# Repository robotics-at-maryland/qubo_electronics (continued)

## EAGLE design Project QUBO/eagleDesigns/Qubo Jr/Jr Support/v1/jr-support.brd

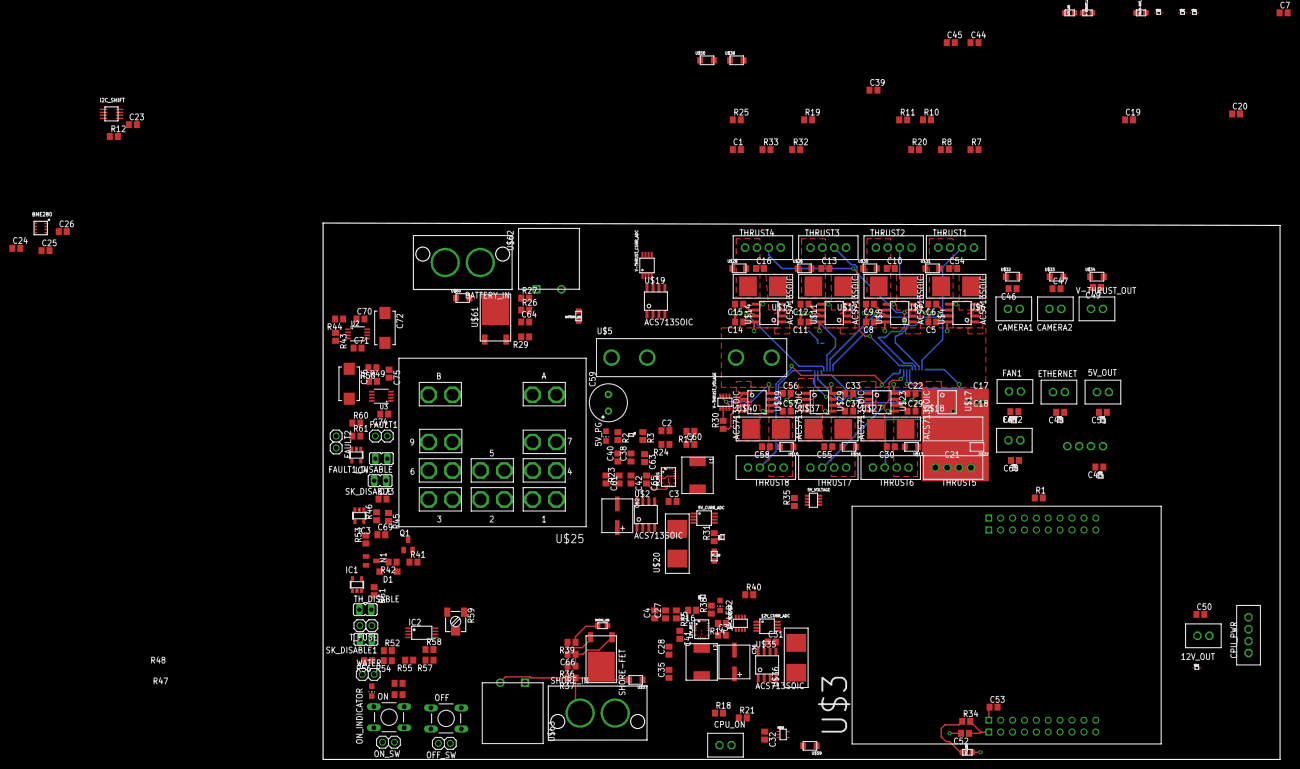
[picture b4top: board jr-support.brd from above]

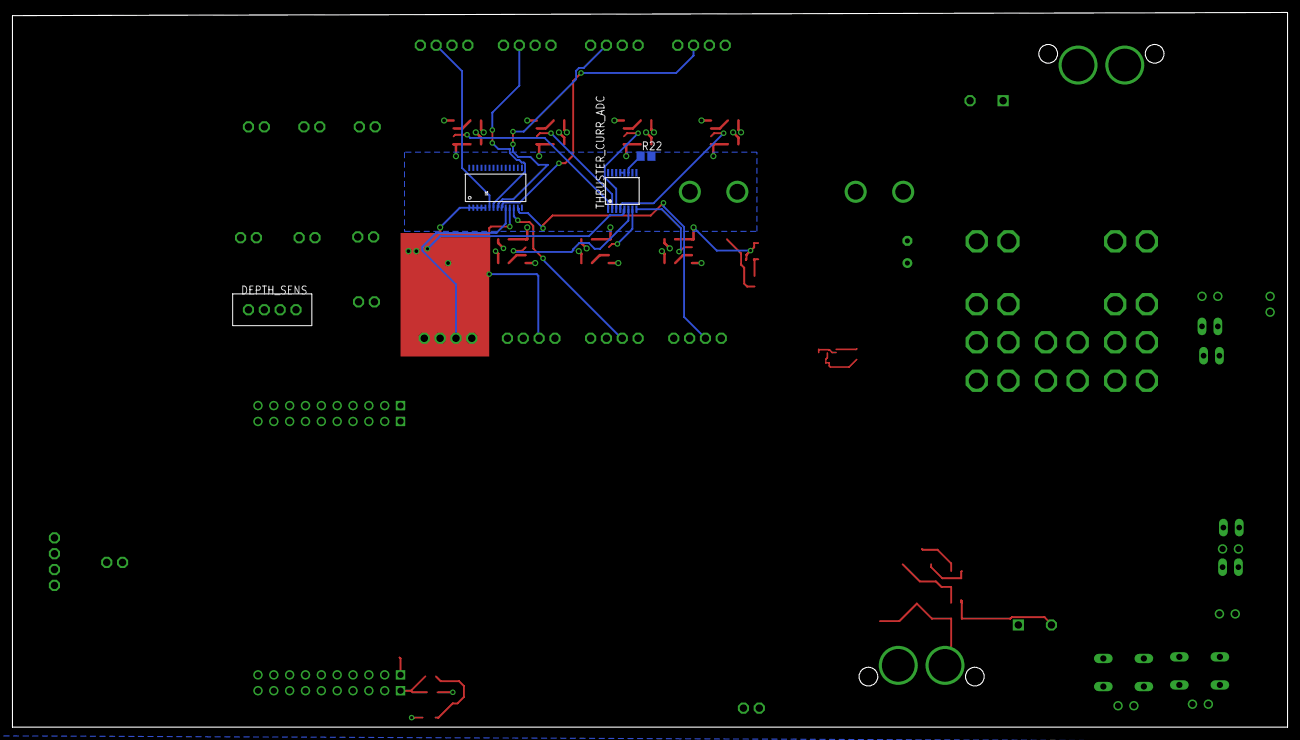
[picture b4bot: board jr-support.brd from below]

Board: 2 copper layers, 204.5 x 114.6 mm, 254 parts (4 on the bottom side), 129 nets.

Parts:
3V3_LED, 5V_LED, 12V_LED: 0805
5V_CURR_ADC, 12V_CURR_ADC: ADC121C021; VSSOP-8
5V_OUT: 5V_OUT; KK254_VERT_2PIN
5V_PG: CHIP-LED0805
5V_REG, 12V_REG: LT8640; QFN18-3X4
5V_VOLTAGE, 12V_VOLTAGE: INA219SOT23; SOT-23-8
12V_OUT: 12V_OUT; KK254_VERT_2PIN
BATTERY_IN: 2_SUPERSABRE; SUPERSABRE_2CIRCUIT
BATTERY_LED: 0805
BME280: BME280; BME280_LGA
C1, C2, C5, C8, C11, C14, C17, C19, C22, C33, C41, C56, C65: 0.1u; C0805
C3, C6, C9, C12, C15, C18, C20, C29, C31, C37, C57: 47n; C0805
C4, C32, C34, C38, C39, C60, C63: 1u; C0805
C7, C10, C13, C16, C21, C30, C43, C44, C45, C46, C47, C48, C49, C50, C51, C52, C53, C54, C55, C58, C67, C68: C0805
C23: 100p; C0805
C24, C25, C26: 100n; C0805
C27, C40: 10u; C0805
C28, C42: 15p; C0805
C35, C61: 22u; C0805
C36, C62: 220u; C-F80
C59: 100u; E3,5-8
C64, C66: 2.2u; C0805
C69, C71, C73, C75: 100nF; C0805
C70, C74: 10nF; C0805
C72, C76: T491D475K050AT; CT7343
CAMERA1, CAMERA2: KK254_VERT_2PIN22-29-2021; KK254_VERT_2PIN
CPU_ON: KK254_VERT_2PIN22-29-2021; KK254_VERT_2PIN
CPU_PWR: CPU PWR; KK254_VERT_4PIN
D1: MMSD4148; SOD123
DEPTH_SENS: Depth Sensor; KK254_VERT_4PIN
ETHERNET: KK254_VERT_2PIN22-29-2021; KK254_VERT_2PIN
FAN1: KK254_VERT_2PIN22-29-2021; KK254_VERT_2PIN
FAN2: Ethernet switch pwr; KK254_VERT_2PIN
FAULT1, FAULT2: 1X02
FAULT1_DISABLE: JP1
I2C_SHIFT: SM8
IC1, IC3, IC4: 74LVC1G08DBV; SOT23-5
IC2: TLC2272PW; TSSOP8
L1, L2: 2.2u; L0740
LED2: FASTCHG; CHIP-LED0805
N1: 2N7002; SOT23
OFF: DTS-6
OFF_SW: 1X02
ON: DTS-6
ON_INDICATOR: Green; CHIP-LED0805
ON_SW: 1X02
Q1: FDN5618P; SOT23
R1, R19, R41, R42, R45, R53, R54: 10k; R0805
R2, R33, R38: 1.2k; R0805
R3, R40, R61: 50k; R0805
R7, R8: 4.7k; R0805
R10, R11: 4.2k; R0805
R12: 200k; R0805
R14, R17: 41.2k; R0805
R15, R23, R46, R49, R51, R60: 1M; R0805
R16: 88.7k; R0805
R18: 510; R0805
R20, R29, R32, R39: 1.5k; R0805
R21: 6.8k; R0805
R22: 0; R0805
R24: 243k; R0805
R25, R30, R35: 10; R0805
R26, R36: 43k; R0805
R27, R37: 4.3k; R0805
R31: 270; R0805
R34: 68; R0805
R43: 845k; R0805
R44, R50: 115k; R0805
R47, R48: 3.3k; R0805
R52, R55, R57, R58: 100k; R0805
R56: 470; R0805
R59: RTRIM3314J
RELAY-OUT_LED: 0805
SHORE-FET: IPD50P04P4-13; TO252-3
SHORE_IN: 2_SUPERSABRE; SUPERSABRE_2CIRCUIT
SHORE_LED: 0805
SK_DISABLE, SK_DISABLE1: JP1
THRUST1, THRUST2, THRUST3, THRUST4, THRUST5, THRUST6, THRUST7, THRUST8: KK254_VERT_4PIN22-29-2041; KK254_VERT_4PIN
THRUSTER_CURR_ADC: ADS7828; TSSOP16
TH_DISABLE: JP1
T_FUSE: 1X02
U1: PCA9685; TSSOP-28_4MM
U2, U3: LT3063; MSOP8
U$1, U$66: DMP32D5SFB; AP02002
U$2, U$4, U$8, U$11, U$14, U$17, U$19, U$23, U$29, U$35, U$39: ACS713SOIC; ACS713-SOIC
U$3: TIVA-C_EVAL
U$5: 25A Fuse; 1.25"_FUSECLIPS
U$6, U$9, U$12, U$15, U$18, U$20, U$27, U$36, U$37, U$40: 4A Fuse; 154-OMNI-BLOK
U$10, U$13, U$16, U$22, U$26, U$28, U$30, U$31, U$32, U$33, U$34, U$38, U$50, U$57, U$59, U$60: VTVS; DO-219AB
U$25: KUHP-5XX1-XX; KUHP_6.35MM-QUICK-CONNECT
U$45: 74LVC1G14; TSSOP5
U$46, U$47, U$48, U$49: ESD9X3; SOD-923_SMD
U$51, U$52, U$53, U$54, U$64, U$65: DESD; X1-DFN1006-2
U$61: IPD50P04P4-13; TO252-3
U$62, U$63: GPTS203212B; GPTS203211B
V-THRUST_CURR_ADC: ADC121C021; VSSOP-8
V-THRUST_LED: 0805
V-THRUST_OUT: Vin_OUT; KK254_VERT_2PIN
V-THRUST_VOLAGE: INA219SOT23; SOT-23-8
WATER: 1X02

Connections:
3V3: BME280.P$2, BME280.P$5, BME280.P$6, BME280.P$8, C24.1, C25.1, C26.1, C52.1, I2C_SHIFT.P$2, R10.2, R11.2, R34.2, U$3.1-1
5V: 5V_CURR_ADC.P$5, 5V_CURR_ADC.P$6, 5V_OUT.P$1, 5V_VOLTAGE.P$4, 12V_CURR_ADC.P$5, 12V_VOLTAGE.P$4, 12V_VOLTAGE.P$8, C1.1, C5.1, C7.1, C8.1, C11.1, C14.1, C17.1, C19.1, C22.1, C33.1, C43.1, C48.1, C51.1, C53.1, C56.1, C67.1, C68.1, DEPTH_SENS.P$4, ETHERNET.P$1, FAN1.P$1, FAN2.P$1, R1.2, R7.2, R8.2, R12.2, R21.2, R31.2, R35.1, THRUSTER_CURR_ADC.10, THRUSTER_CURR_ADC.16, U1.1, U1.2, U1.3, U1.4, U1.5, U1.24, U1.28, U$3.3-1, U$4.P$8, U$8.P$8, U$11.P$8, U$14.P$8, U$17.P$8, U$19.P$8, U$20.P$2, U$23.P$8, U$29.P$8, U$35.P$8, U$39.P$8, U$45.P$5, U$51.P$2, U$52.P$2, U$53.P$2, U$54.P$2, U$64.P$2, U$65.P$2, V-THRUST_CURR_ADC.P$3, V-THRUST_CURR_ADC.P$5, V-THRUST_CURR_ADC.P$6, V-THRUST_VOLAGE.P$4, V-THRUST_VOLAGE.P$7, V-THRUST_VOLAGE.P$8
12V: 12V_OUT.P$1, C44.1, C45.1, C50.1, CPU_PWR.P$3, CPU_PWR.P$4, R25.1, R33.2, U$36.P$2, U$46.P$1, U$47.P$1, U$48.P$1, U$49.P$1
+5V: C69.1, C71.1, FAULT1.1, FAULT1_DISABLE.2, IC2.8, IC3.5, R43.2, R55.1, R57.2, R59.3, R61.2, SK_DISABLE.2, TH_DISABLE.2, T_FUSE.1, U2.3, U2.4
CPU_ON: 12V_REG.14, U$45.P$4
FAULT: IC1.4, IC3.2, IC4.4, OFF.3, OFF.4, OFF_SW.1
FET: IC3.4, N1.1, R53.2
GND: 3V3_LED.P$2, 5V_CURR_ADC.P$3, 5V_CURR_ADC.P$7, 5V_LED.P$2, 5V_OUT.P$2, 5V_PG.C, 5V_REG.6, 5V_REG.7, 5V_REG.10, 5V_REG.11, 5V_REG.18, 5V_VOLTAGE.P$3, 5V_VOLTAGE.P$7, 5V_VOLTAGE.P$8, 12V_CURR_ADC.P$3, 12V_CURR_ADC.P$6, 12V_CURR_ADC.P$7, 12V_LED.P$2, 12V_OUT.P$2, 12V_REG.6, 12V_REG.7, 12V_REG.10, 12V_REG.11, 12V_REG.18, 12V_VOLTAGE.P$3, 12V_VOLTAGE.P$7, BATTERY_IN.P$2, BATTERY_LED.P$2, BME280.P$1, BME280.P$7, C1.2, C2.2, C3.2, C4.2, C5.2, C6.2, C7.2, C8.2, C9.2, C10.2, C11.2, C12.2, C13.2, C14.2, C15.2, C16.2, C17.2, C18.2, C19.2, C20.2, C21.2, C22.2, C23.2, C24.2, C25.2, C26.2, C27.2, C29.2, C30.2, C31.2, C33.2, C34.2, C35.2, C36.P$2, C37.2, C38.2, C39.2, C40.2, C43.2, C44.2, C45.2, C46.2, C47.2, C48.2, C49.2, C50.2, C51.2, C52.2, C53.2, C54.2, C55.2, C56.2, C57.2, C58.2, C59.-, C60.2, C61.2, C62.P$2, C63.2, C64.2, C66.2, C67.2, C68.2, C69.2, C70.2, C71.2, C72.-, C73.2, C74.2, C75.2, C76.-, CAMERA1.P$2, CAMERA2.P$2, CPU_PWR.P$1, CPU_PWR.P$2, DEPTH_SENS.P$3, ETHERNET.P$2, FAN1.P$2, FAN2.P$2, I2C_SHIFT.P$1, IC1.3, IC2.4, IC3.3, IC4.3, LED2.C, N1.2, OFF.1, OFF.2, OFF_SW.2, ON.1, ON.2, ON_INDICATOR.C, ON_SW.2, R14.1, R16.1, R17.1, R19.2, R22.2, R24.1, R44.1, R46.1, R50.1, R51.1, R53.1, R58.1, R59.1, R60.1, RELAY-OUT_LED.P$2, SHORE_IN.P$2, SHORE_LED.P$2, THRUST1.P$1, THRUST1.P$3, THRUST2.P$1, THRUST2.P$3, THRUST3.P$1, THRUST3.P$3, THRUST4.P$1, THRUST4.P$3, THRUST5.P$1, THRUST5.P$3, THRUST6.P$1, THRUST6.P$3, THRUST7.P$1, THRUST7.P$3, THRUST8.P$1, THRUST8.P$3, THRUSTER_CURR_ADC.9, THRUSTER_CURR_ADC.12, THRUSTER_CURR_ADC.13, U1.14, U1.23, U1.25, U2.8, U3.8, U$2.P$5, U$3.2-1, U$3.3-2, U$4.P$5, U$8.P$5, U$10.P$1, U$11.P$5, U$13.P$1, U$14.P$5, U$16.P$1, U$17.P$5, U$19.P$5, U$22.P$1, U$23.P$5, U$26.P$1, U$28.P$1, U$29.P$5, U$30.P$1, U$31.P$1, U$32.P$1, U$33.P$1, U$34.P$1, U$35.P$5, U$38.P$1, U$39.P$5, U$46.P$2, U$47.P$2, U$48.P$2, U$49.P$2, U$50.P$1, U$51.P$1, U$52.P$1, U$53.P$1, U$54.P$1, U$57.P$1, U$60.P$1, U$62.P$1, U$63.P$1, U$64.P$1, U$65.P$1, V-THRUST_CURR_ADC.P$7, V-THRUST_LED.P$2, V-THRUST_OUT.P$2, V-THRUST_VOLAGE.P$3, WATER.2
unnamed: 12V_REG.15, R14.2
unnamed: R1.1, U$3.2-5
unnamed: FAULT2.1, IC4.2, R61.1
unnamed: 5V_PG.A, R2.1
unnamed: R2.2, U$1.P$3
unnamed: 5V_REG.19, R3.1, U$1.P$2
unnamed: 12V_REG.1, C28.1, C35.1, C36.P$1, L2.P$2, R15.2, U$35.P$1, U$35.P$2
unnamed: 5V_REG.15, R17.2
unnamed: C3.1, U$2.P$6
unnamed: C9.1, U$8.P$6
unnamed: C6.1, U$4.P$6
unnamed: C54.1, THRUST1.P$4, U$6.P$2, U$31.P$2
unnamed: U$4.P$3, U$4.P$4, U$6.P$1
unnamed: C10.1, THRUST2.P$4, U$9.P$2, U$30.P$2
unnamed: U$8.P$3, U$8.P$4, U$9.P$1
unnamed: C12.1, U$11.P$6
unnamed: C13.1, THRUST3.P$4, U$12.P$2, U$26.P$2
unnamed: U$11.P$3, U$11.P$4, U$12.P$1
unnamed: C15.1, U$14.P$6
unnamed: C16.1, THRUST4.P$4, U$15.P$2, U$28.P$2
unnamed: R22.1, THRUSTER_CURR_ADC.11
unnamed: U$14.P$3, U$14.P$4, U$15.P$1
unnamed: C18.1, U$17.P$6
unnamed: C21.1, THRUST5.P$4, U$18.P$2, U$22.P$2
unnamed: U$17.P$3, U$17.P$4, U$18.P$1
unnamed: C29.1, U$23.P$6
unnamed: C30.1, THRUST6.P$4, U$13.P$2, U$27.P$2
unnamed: U$23.P$3, U$23.P$4, U$27.P$1
unnamed: C37.1, U$29.P$6
unnamed: 12V_REG.8, 12V_REG.9, 12V_REG.21, 12V_REG.22, C41.2, L2.P$1
unnamed: C20.1, U$19.P$6
unnamed: U$5.P$1, U$5.P$2, U$19.P$3, U$19.P$4
unnamed: R19.1, U$25.AA, U$25.AB
unnamed: C55.1, THRUST7.P$4, U$16.P$2, U$37.P$2
unnamed: U$29.P$3, U$29.P$4, U$37.P$1
unnamed: C57.1, U$39.P$6
unnamed: C58.1, THRUST8.P$4, U$10.P$2, U$40.P$2
unnamed: 5V_REG.8, 5V_REG.9, 5V_REG.21, 5V_REG.22, C65.2, L1.P$1
unnamed: C23.1, I2C_SHIFT.P$7, I2C_SHIFT.P$8, R12.1
unnamed: 5V_REG.20, C42.2, R23.1, R24.2
unnamed: 5V_REG.3, C65.1
unnamed: 12V_REG.20, C28.2, R15.1, R16.2
unnamed: 12V_REG.3, C41.1
unnamed: Q1.1, R41.1, R42.1
unnamed: U$39.P$3, U$39.P$4, U$40.P$1
unnamed: 5V_REG.2, C63.1
unnamed: 12V_VOLTAGE.P$1, 12V_VOLTAGE.P$2, R25.2
unnamed: R37.1, SHORE-FET.TAB, SHORE_IN.P$1, U$57.P$2
unnamed: C32.2, CPU_ON.P$2, U$45.P$3, U$59.P$1
unnamed: C31.1, U$35.P$6
unnamed: U$19.P$7, V-THRUST_CURR_ADC.P$4
unnamed: 12V_REG.2, C39.1
unnamed: U$2.P$3, U$2.P$4, U$20.P$1
unnamed: U$35.P$3, U$35.P$4, U$36.P$1
unnamed: 5V_CURR_ADC.P$4, U$2.P$7
unnamed: R30.2, V-THRUST_VOLAGE.P$1, V-THRUST_VOLAGE.P$2
unnamed: C32.1, R18.2, U$45.P$2
unnamed: 12V_CURR_ADC.P$4, U$35.P$7
unnamed: CPU_ON.P$1, R18.1, R21.1, U$59.P$2
unnamed: C66.1, R36.1, SHORE-FET.1
unnamed: R36.2, R37.2, U$63.P$2
unnamed: BATTERY_IN.P$1, R27.1, U$60.P$2, U$61.TAB
unnamed: C64.1, R26.1, U$61.1
unnamed: R26.2, R27.2, U$62.P$2
unnamed: R20.1, RELAY-OUT_LED.P$1
unnamed: BATTERY_LED.P$1, R29.1
unnamed: 5V_LED.P$1, R31.1
unnamed: R32.1, V-THRUST_LED.P$1
unnamed: 12V_LED.P$1, R33.1
unnamed: 3V3_LED.P$1, R34.1
unnamed: R39.1, SHORE_LED.P$1
unnamed: FAULT1.2, FAULT1_DISABLE.1, IC4.1, R60.2
unnamed: 5V_VOLTAGE.P$1, 5V_VOLTAGE.P$2, R35.2
unnamed: LED2.A, R38.1
unnamed: R38.2, U$66.P$3
unnamed: 12V_REG.19, R40.1, U$66.P$2
unnamed: D1.A, N1.3, R42.2
unnamed: R43.1, R44.2, U2.2
unnamed: C70.1, U2.1
unnamed: ON_INDICATOR.A, R47.1, R48.1
unnamed: R49.1, R50.2, U3.2
unnamed: C74.1, U3.1
unnamed: IC1.2, R51.2, TH_DISABLE.1, T_FUSE.2
unnamed: IC2.2, IC2.7, R52.1
unnamed: IC2.6, R52.2, R54.1
unnamed: IC2.5, R57.1, R58.2
unnamed: R54.2, R55.2, R56.1
unnamed: R56.2, WATER.1
unnamed: IC2.3, R59.2
unnamed: IC2.1, SK_DISABLE1.1
ON_SW: D1.C, ON.3, ON.4, ON_SW.1
RELAY-BATT: Q1.2, R29.2, R41.2, U$25.5A, U$25.5B, U$61.3
RELAY-CTRL: C75.1, R49.2, U3.3, U3.4, U$25.BA, U$25.BB
RELAY-SHORE: R39.2, SHORE-FET.3, U$25.2A, U$25.2B
RELAY_OUT: 5V_REG.4, 5V_REG.13, 5V_REG.14, 12V_REG.4, 12V_REG.13, C4.1, C27.1, C34.1, C38.1, C40.1, C59.+, C60.1, R3.2, R20.2, R40.2, U$1.P$1, U$19.P$1, U$19.P$2, U$25.7A, U$25.7B, U$50.P$2, U$66.P$1
SCL1: 5V_CURR_ADC.P$1, 5V_VOLTAGE.P$5, 12V_CURR_ADC.P$1, 12V_VOLTAGE.P$5, I2C_SHIFT.P$6, R8.1, THRUSTER_CURR_ADC.14, U1.26, U$3.1-9, V-THRUST_CURR_ADC.P$1, V-THRUST_VOLAGE.P$5
SCL-3V3: BME280.P$4, DEPTH_SENS.P$1, I2C_SHIFT.P$3, R11.1
SDA1: 5V_CURR_ADC.P$8, 5V_VOLTAGE.P$6, 12V_CURR_ADC.P$8, 12V_VOLTAGE.P$6, I2C_SHIFT.P$5, R7.1, THRUSTER_CURR_ADC.15, U1.27, U$3.1-10, V-THRUST_CURR_ADC.P$8, V-THRUST_VOLAGE.P$6
SDA-3V3: BME280.P$3, DEPTH_SENS.P$2, I2C_SHIFT.P$4, R10.1
SK: C73.1, IC3.1, R45.1, R46.2, SK_DISABLE.1
SW-5V: 5V_REG.1, C2.1, C42.1, C61.1, C62.P$1, L1.P$2, R23.2, U$2.P$1, U$2.P$2, U$2.P$8
T1_CURR: THRUSTER_CURR_ADC.1, U$4.P$7
T1_PWM: THRUST1.P$2, U1.6
T2_CURR: THRUSTER_CURR_ADC.2, U$8.P$7
T2_PWM: THRUST2.P$2, U1.7
T3_CURR: THRUSTER_CURR_ADC.3, U$11.P$7
T3_PWM: THRUST3.P$2, U1.8
T4_CURR: THRUSTER_CURR_ADC.4, U$14.P$7
T4_PWM: THRUST4.P$2, U1.9
T5_CURR: THRUSTER_CURR_ADC.5, U$17.P$7
T5_PWM: THRUST5.P$2, U1.10
T6_CURR: THRUSTER_CURR_ADC.6, U$23.P$7
T6_PWM: THRUST6.P$2, U1.11
T7_CURR: THRUSTER_CURR_ADC.7, U$29.P$7
T7_PWM: THRUST7.P$2, U1.12
T8_CURR: THRUSTER_CURR_ADC.8, U$39.P$7
T8_PWM: THRUST8.P$2, U1.13
VCC: IC1.5, IC4.5
VDD: C72.+, C76.+, Q1.3, R47.2, R48.2, U2.5, U2.6, U2.7, U3.5, U3.6, U3.7
V_THRUST: C46.1, C47.1, C49.1, CAMERA1.P$1, CAMERA2.P$1, R30.1, R32.2, U$4.P$1, U$4.P$2, U$5.P$3, U$5.P$4, U$8.P$1, U$8.P$2, U$11.P$1, U$11.P$2, U$14.P$1, U$14.P$2, U$17.P$1, U$17.P$2, U$23.P$1, U$23.P$2, U$29.P$1, U$29.P$2, U$32.P$2, U$33.P$2, U$34.P$2, U$38.P$2, U$39.P$1, U$39.P$2, V-THRUST_OUT.P$1
WATER: IC1.1, SK_DISABLE1.2

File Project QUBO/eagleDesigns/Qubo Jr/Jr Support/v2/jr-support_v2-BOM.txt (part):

Partlist exported from C:/Users/Ben/Documents/Dropbox/Documents/UMD/R@M/RAM Tran Electronics_2016/qubo_electronics.git/Project QUBO/eagleDesigns/Jr Support/Jr Support/v2/jr-support_v2.sch at Tue, 5/9/2017 1:04 PM

Part              Value                     Device                    Package                   Description                                                                               PROD_ID  VALUE  
3V3_LED                                     0805_LED                  0805                      LED, 0805 package. Any variety.                                                                           
5V_CURR_ADC       ADC121C021                ADC121C021                VSSOP-8                   ADC121C021 8-pin VSSOP package                                                                            
5V_LED                                      0805_LED                  0805                      LED, 0805 package. Any variety.                                                                           
5V_OUT            5V_OUT                    KK254_VERT_2PIN22-29-2021 KK254_VERT_2PIN           KK® 254 Wire-to-Board Header, Vertical, with Friction Lock, 2 Circuits, Gold (Au) Plating                 
5V_PG                                       LEDCHIP-LED0805           CHIP-LED0805              LED                                                                                                       
5V_REG            LT8640                    LT8640                    QFN18-3X4                 Linear LT8640                                                                                             
5V_VOLTAGE        INA219SOT23               INA219SOT23               SOT-23-8                  TI INA219                                                                                                 
12V_CURR_ADC      ADC121C021                ADC121C021                VSSOP-8                   ADC121C021 8-pin VSSOP package                                                                            
12V_LED                                     0805_LED                  0805                      LED, 0805 package. Any variety.                                                                           
12V_OUT           12V_OUT                   KK254_VERT_2PIN22-29-2021 KK254_VERT_2PIN           KK® 254 Wire-to-Board Header, Vertical, with Friction Lock, 2 Circuits, Gold (Au) Plating                 
12V_REG           LT8640                    LT8640                    QFN18-3X4                 Linear LT8640                                                                                             
12V_VOLTAGE       INA219SOT23               INA219SOT23               SOT-23-8                  TI INA219                                                                                                 
BATTERY_IN        2_SUPERSABRE              2_SUPERSABRE              SUPERSABRE_2CIRCUIT       Molex SuperSabre                                                                                          
BATTERY_LED                                 0805_LED                  0805                      LED, 0805 package. Any variety.                                                                           
BME280            BME280                    BME280                    BME280_LGA                                                                                                          IC-13090 BME280 
C1                0.1u                      C-USC0805                 C0805                     CAPACITOR, American symbol                                                                                
C2                0.1u                      C-USC0805                 C0805                     CAPACITOR, American symbol                                                                                
C3                47n                       C-USC0805                 C0805                     CAPACITOR, American symbol                                                                                
C4                1u                        C-USC0805                 C0805                     CAPACITOR, American symbol                                                                                
C5                0.1u                      C-USC0805                 C0805                     CAPACITOR, American symbol                                                                                
C6                47n                       C-USC0805                 C0805                     CAPACITOR, American symbol                                                                                
C7                                          C-USC0805                 C0805                     CAPACITOR, American symbol                                                                                
C8                0.1u                      C-USC0805                 C0805                     CAPACITOR, American symbol                                                                                
C9                47n                       C-USC0805                 C0805                     CAPACITOR, American symbol                                                                                
C10                                         C-USC0805                 C0805                     CAPACITOR, American symbol                                                                                
C11               0.1u                      C-USC0805                 C0805                     CAPACITOR, American symbol                                                                                
C12               47n                       C-USC0805                 C0805                     CAPACITOR, American symbol                                                                                
C13                                         C-USC0805                 C0805                     CAPACITOR, American symbol                                                                                
C14               0.1u                      C-USC0805                 C0805                     CAPACITOR, American symbol                                                                                
C15               47n                       C-USC0805                 C0805                     CAPACITOR, American symbol                                                                                
C16                                         C-USC0805                 C0805                     CAPACITOR, American symbol                                                                                
C17               0.1u                      C-USC0805                 C0805                     CAPACITOR, American symbol                                                                                
C18               47n                       C-USC0805                 C0805                     CAPACITOR, American symbol                                                                                
C19               0.1u                      C-USC0805                 C0805                     CAPACITOR, American symbol                                                                                
C20               47n                       C-USC0805                 C0805                     CAPACITOR, American symbol                                                                                
C21                                         C-USC0805                 C0805                     CAPACITOR, American symbol                                                                                
C22               0.1u                      C-USC0805                 C0805                     CAPACITOR, American symbol                                                                                
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
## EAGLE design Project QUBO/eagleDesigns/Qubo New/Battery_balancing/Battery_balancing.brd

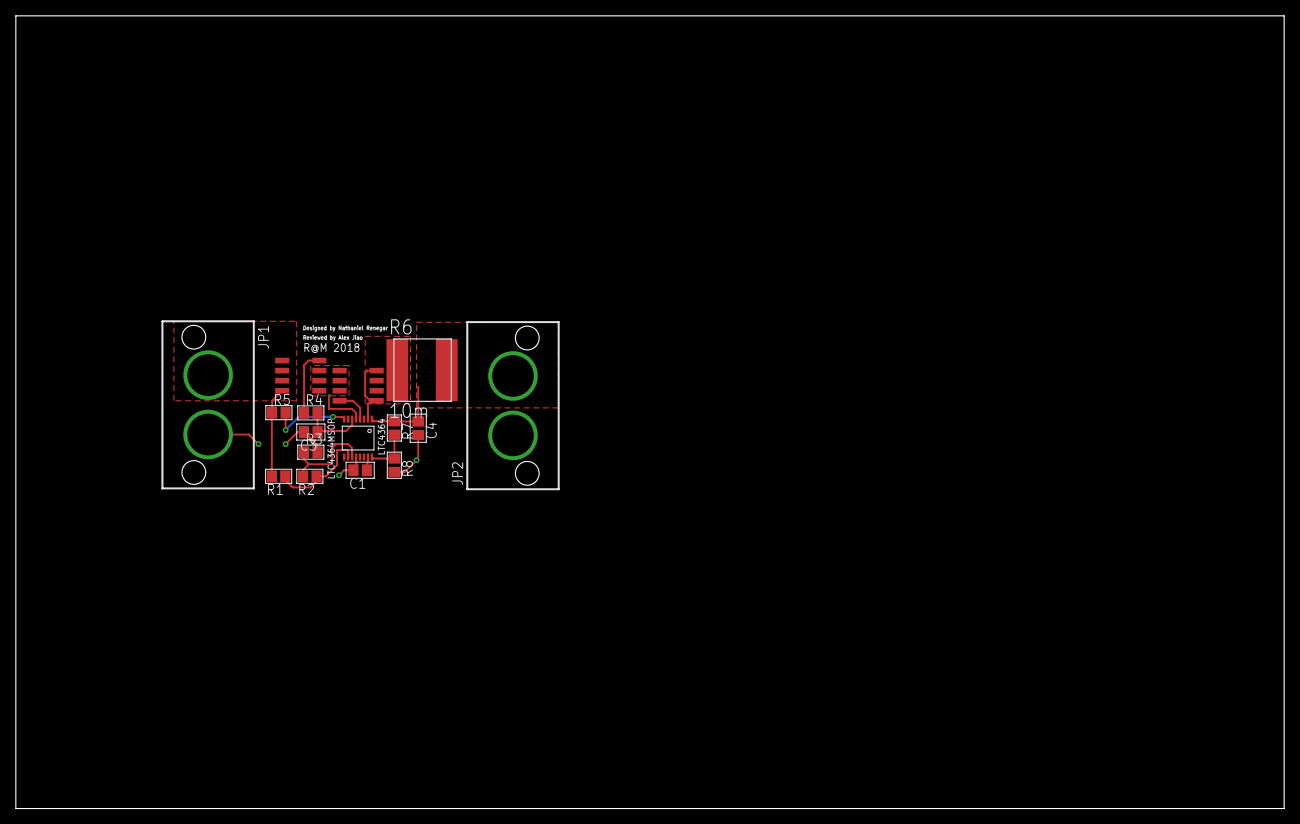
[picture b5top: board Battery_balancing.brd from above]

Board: 2 copper layers, 160.0 x 100.0 mm, 16 parts (0 on the bottom side), 13 nets.

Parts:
C1: 150nF; C0805
C3: 6.8nF; C0805
C4: 22uF; C0805
JP1, JP2: 2_SUPERSABRE; SUPERSABRE_2CIRCUIT
LTC4364: LTC4364MSOP; MSOP16
M1, M2: IRF7458PBF; SOIC8
R1: 172K; R0805
R2: 10k; R0805
R3, R5: 10K; R0805
R4: 10; R0805
R6: 10m; 2827W
R7: 91K; R0805
R8: 5K; R0805

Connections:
BAT1: JP1.P$1, M1.D1, M1.D2, M1.D3, M1.D4, R1.2, R5.1
GND: C1.2, C3.2, C4.2, JP1.P$2, JP2.P$1, LTC4364.GND, R3.2, R8.2
unnamed: LTC4364.DGATE, M2.G1
unnamed: LTC4364.SOURCE, M1.S1, M1.S2, M1.S3, M2.S1, M2.S2, M2.S3
unnamed: C1.1, LTC4364.TMR
unnamed: LTC4364.UV, R1.1, R2.1
unnamed: LTC4364.OV, R2.2, R3.1
unnamed: M1.G1, R4.1
unnamed: LTC4364.FB, R7.2, R8.1
unnamed: C3.1, LTC4364.HGATE, R4.2
unnamed: LTC4364.SENSE, M2.D1, M2.D2, M2.D3, M2.D4, R6.P$1
unnamed: LTC4364.VCC, R5.2
unnamed: C4.1, JP2.P$2, LTC4364.OUT, R6.P$2, R7.1
